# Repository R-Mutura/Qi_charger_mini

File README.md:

# The_Qi_wireless_charger_tx
This repo contains the design files for the Qi wireless charger.

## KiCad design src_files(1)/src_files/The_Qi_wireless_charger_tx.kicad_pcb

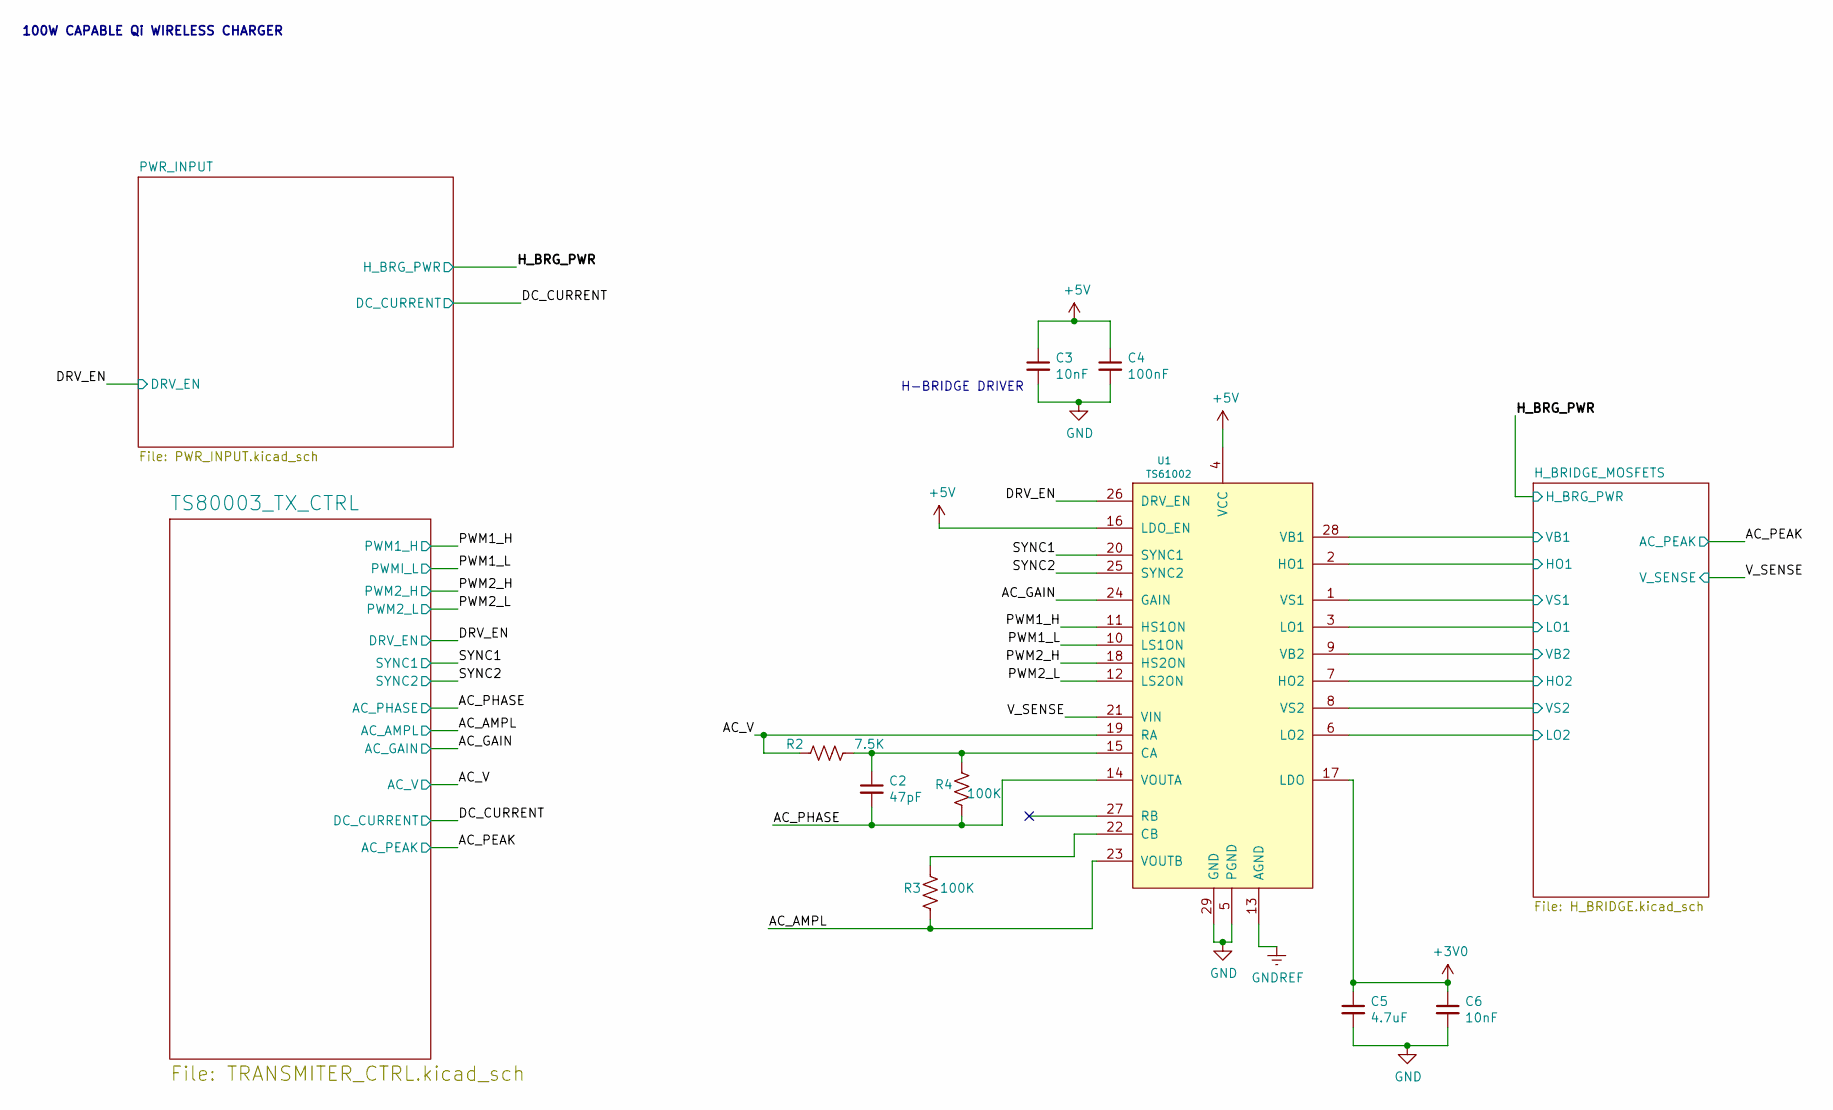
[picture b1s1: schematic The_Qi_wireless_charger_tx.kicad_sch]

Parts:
C2: 47pF; C_0402_1005Metric
C3, C6: 10nF; C_0402_1005Metric
C4: 100nF; C_0402_1005Metric
C5: 4.7uF; C_0402_1005Metric
R2: 7.5K; R_0402_1005Metric
R3, R4: 100K; R_0402_1005Metric
U1: TS61002; QFN50P500X500X100-29N

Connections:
+3V0: C5.1, C6.1, U1.17 (LDO)
+5V: C3.1, C4.1, U1.4 (VCC), U1.16 (LDO_EN); also elsewhere on the board
/AC_AMPL: R3.2, U1.23 (VOUTB); also elsewhere on the board
/AC_GAIN: U1.24 (GAIN); also elsewhere on the board
/AC_PHASE: C2.2, R4.2, U1.14 (VOUTA); also elsewhere on the board
/AC_V: R2.1, U1.19 (RA); also elsewhere on the board
/DRV_EN: U1.26 (DRV_EN); also elsewhere on the board
/H_BRIDGE_MOSFETS/HO1: U1.2 (HO1); also elsewhere on the board
/H_BRIDGE_MOSFETS/HO2: U1.7 (HO2); also elsewhere on the board
/H_BRIDGE_MOSFETS/LO1: U1.3 (LO1); also elsewhere on the board
/H_BRIDGE_MOSFETS/LO2: U1.6 (LO2); also elsewhere on the board
/H_BRIDGE_MOSFETS/VB1: U1.28 (VB1); also elsewhere on the board
/H_BRIDGE_MOSFETS/VB2: U1.9 (VB2); also elsewhere on the board
/H_BRIDGE_MOSFETS/VS1: U1.1 (VS1); also elsewhere on the board
/H_BRIDGE_MOSFETS/VS2: U1.8 (VS2); also elsewhere on the board
/PWM1_H: U1.11 (HS1ON); also elsewhere on the board
/PWM1_L: U1.10 (LS1ON); also elsewhere on the board
/PWM2_H: U1.18 (HS2ON); also elsewhere on the board
/PWM2_L: U1.12 (LS2ON); also elsewhere on the board
/SYNC1: U1.20 (SYNC1); also elsewhere on the board
/SYNC2: U1.25 (SYNC2); also elsewhere on the board
/V_SENSE: U1.21 (VIN); also elsewhere on the board
GND: C3.2, C4.2, C5.2, C6.2, U1.5 (PGND), U1.29 (GND); also elsewhere on the board
GNDREF: U1.13 (AGND); also elsewhere on the board
unnamed: C2.1, R2.2, R4.1, U1.15 (CA)
unnamed: R3.1, U1.22 (CB)

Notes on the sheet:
100W CAPABLE Qi WIRELESS CHARGER
H-BRIDGE DRIVER

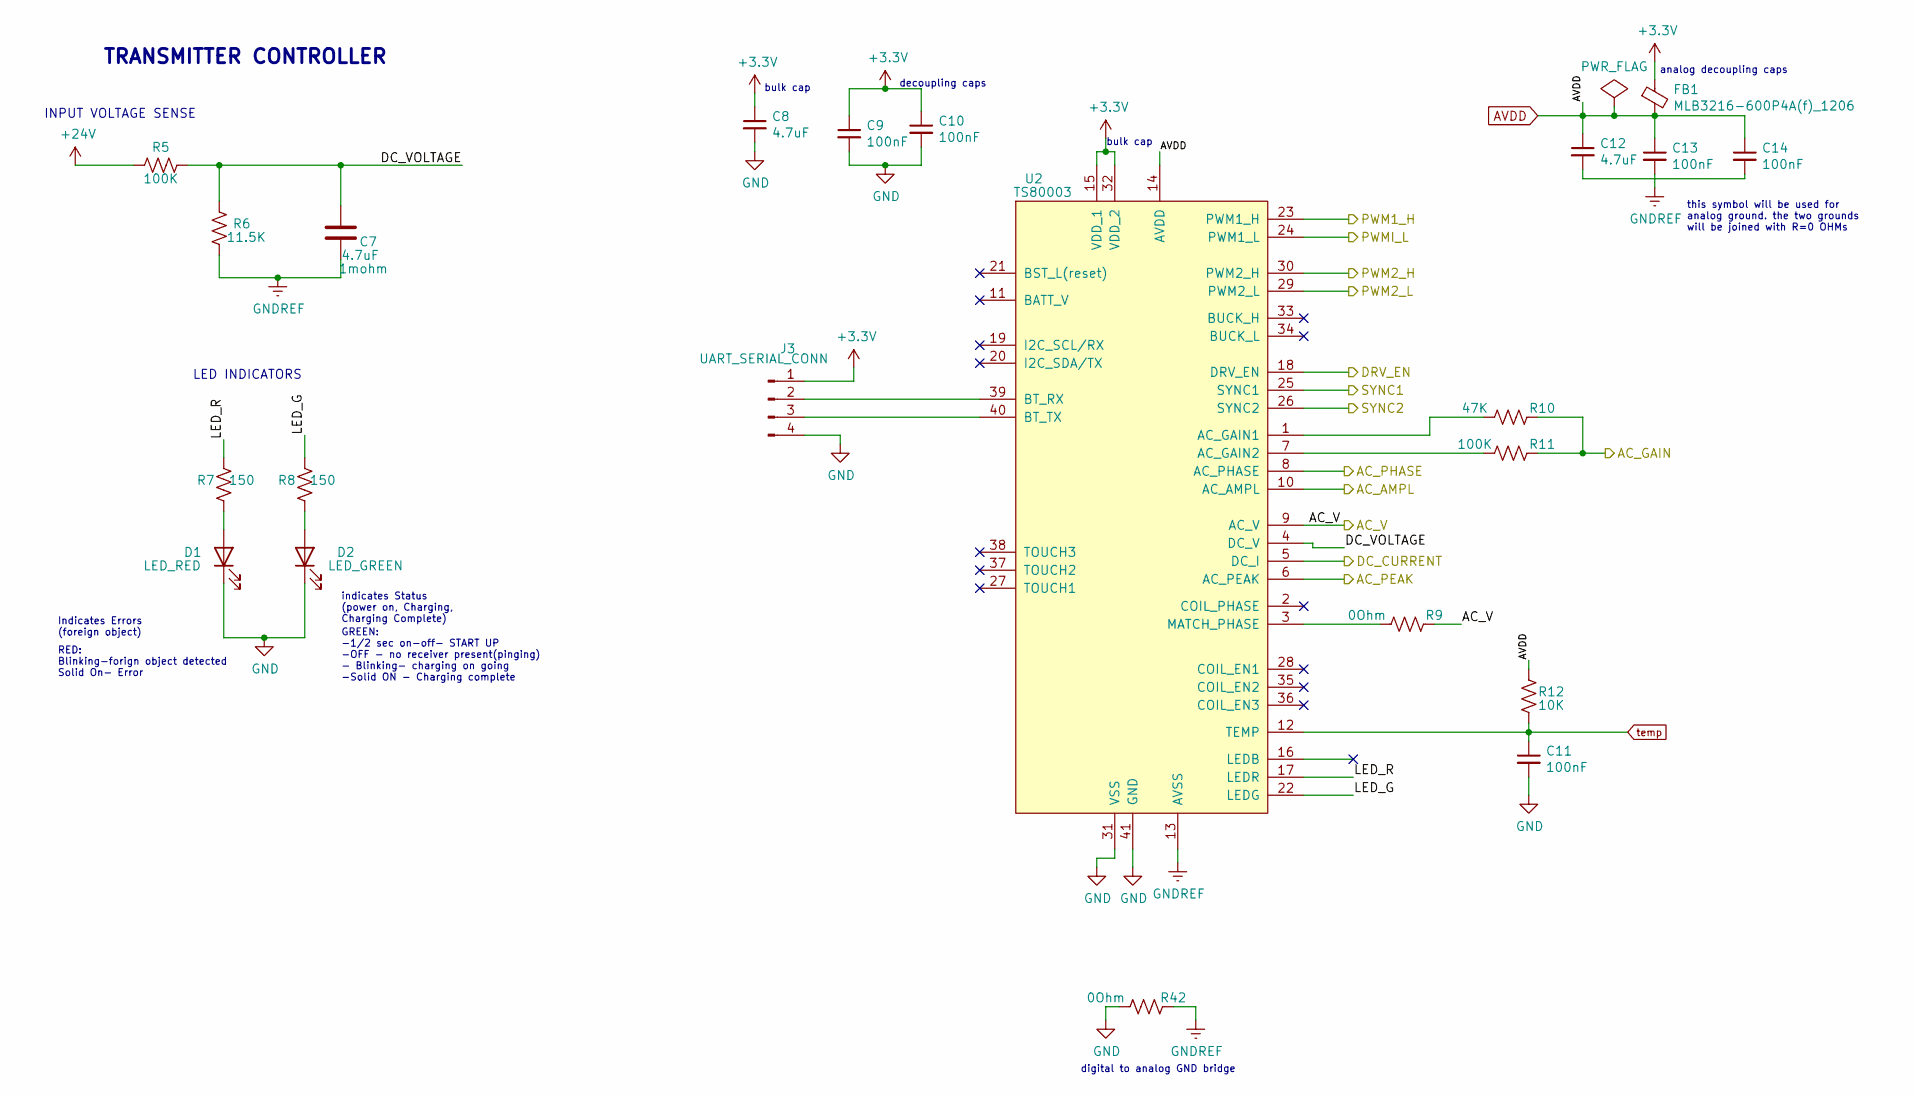
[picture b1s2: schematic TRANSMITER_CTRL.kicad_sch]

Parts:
C7, C8, C12: 4.7uF; C_0402_1005Metric
C9, C10, C11, C13, C14: 100nF; C_0402_1005Metric
D1: LED_RED; LED_0603_1608Metric
D2: LED_GREEN; LED_0603_1608Metric
FB1: MLB3216-600P4A(f)_1206; L_1206_3216Metric
J3: UART_SERIAL_CONN; PinHeader_1x04_P2.54mm_Vertical
R5, R11: 100K; R_0603_1608Metric
R6: 11.5K; R_0603_1608Metric
R7, R8: 150; R_0402_1005Metric
R9, R42: 0Ohm; R_0603_1608Metric
R10: 47K; R_0603_1608Metric
R12: 10K; R_0603_1608Metric
U2: TS80003; QFN40P500X500X90-41N-D

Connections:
+3V3: C8.1, C9.1, C10.1, FB1.1, J3.1, U2.15 (VDD_1), U2.32 (VDD_2); also elsewhere on the board
+24V: R5.2; also elsewhere on the board
/AC_AMPL: U2.10 (AC_AMPL); also elsewhere on the board
/AC_GAIN: R10.1, R11.1; also elsewhere on the board
/AC_PEAK: U2.6 (AC_PEAK); also elsewhere on the board
/AC_PHASE: U2.8 (AC_PHASE); also elsewhere on the board
/AC_V: R9.1, U2.9 (AC_V); also elsewhere on the board
/DC_CURRENT: U2.5 (DC_I); also elsewhere on the board
/DRV_EN: U2.18 (DRV_EN); also elsewhere on the board
/PWM1_H: U2.23 (PWM1_H); also elsewhere on the board
/PWM1_L: U2.24 (PWM1_L); also elsewhere on the board
/PWM2_H: U2.30 (PWM2_H); also elsewhere on the board
/PWM2_L: U2.29 (PWM2_L); also elsewhere on the board
/SYNC1: U2.25 (SYNC1); also elsewhere on the board
/SYNC2: U2.26 (SYNC2); also elsewhere on the board
/TS80003_TX_CTRL/DC_VOLTAGE: C7.1, R5.1, R6.2, U2.4 (DC_V)
/TS80003_TX_CTRL/LED_G: R8.1, U2.22 (LEDG)
/TS80003_TX_CTRL/LED_R: R7.1, U2.17 (LEDR)
AVDD: C12.1, C13.1, C14.1, FB1.2, R12.1, U2.14 (AVDD); also elsewhere on the board
GND: C8.2, C9.2, C10.2, C11.2, D1.1 (K), D2.1 (K), J3.4, R42.2, U2.31 (VSS), U2.41 (GND); also elsewhere on the board
GNDREF: C7.2, C13.2, R6.1, R42.1, U2.13 (AVSS); also elsewhere on the board
unnamed: C12.2, C14.2
unnamed: D1.2 (A), R7.2
unnamed: D2.2 (A), R8.2
unnamed: J3.2, U2.39 (BT_RX)
unnamed: J3.3, U2.40 (BT_TX)
unnamed: R9.2, U2.3 (MATCH_PHASE)
unnamed: R10.2, U2.1 (AC_GAIN1)
unnamed: R11.2, U2.7 (AC_GAIN2)
temp: C11.1, R12.2, U2.12 (TEMP); also elsewhere on the board

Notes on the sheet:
TRANSMITTER CONTROLLER
INPUT VOLTAGE SENSE
indicates Status (power on, Charging, Charging Complete)
digital to analog GND bridge
LED INDICATORS
analog decoupling caps
this symbol will be used for analog ground. the two grounds will be joined with R=0 OHMs
bulk cap
RED: Blinking-forign object detected Solid On- Error
decoupling caps
GREEN: -1/2 sec on-off- START UP -OFF - no receiver present(pinging) - Blinking- charging on going -Solid ON - Charging complete
Indicates Errors (foreign object)

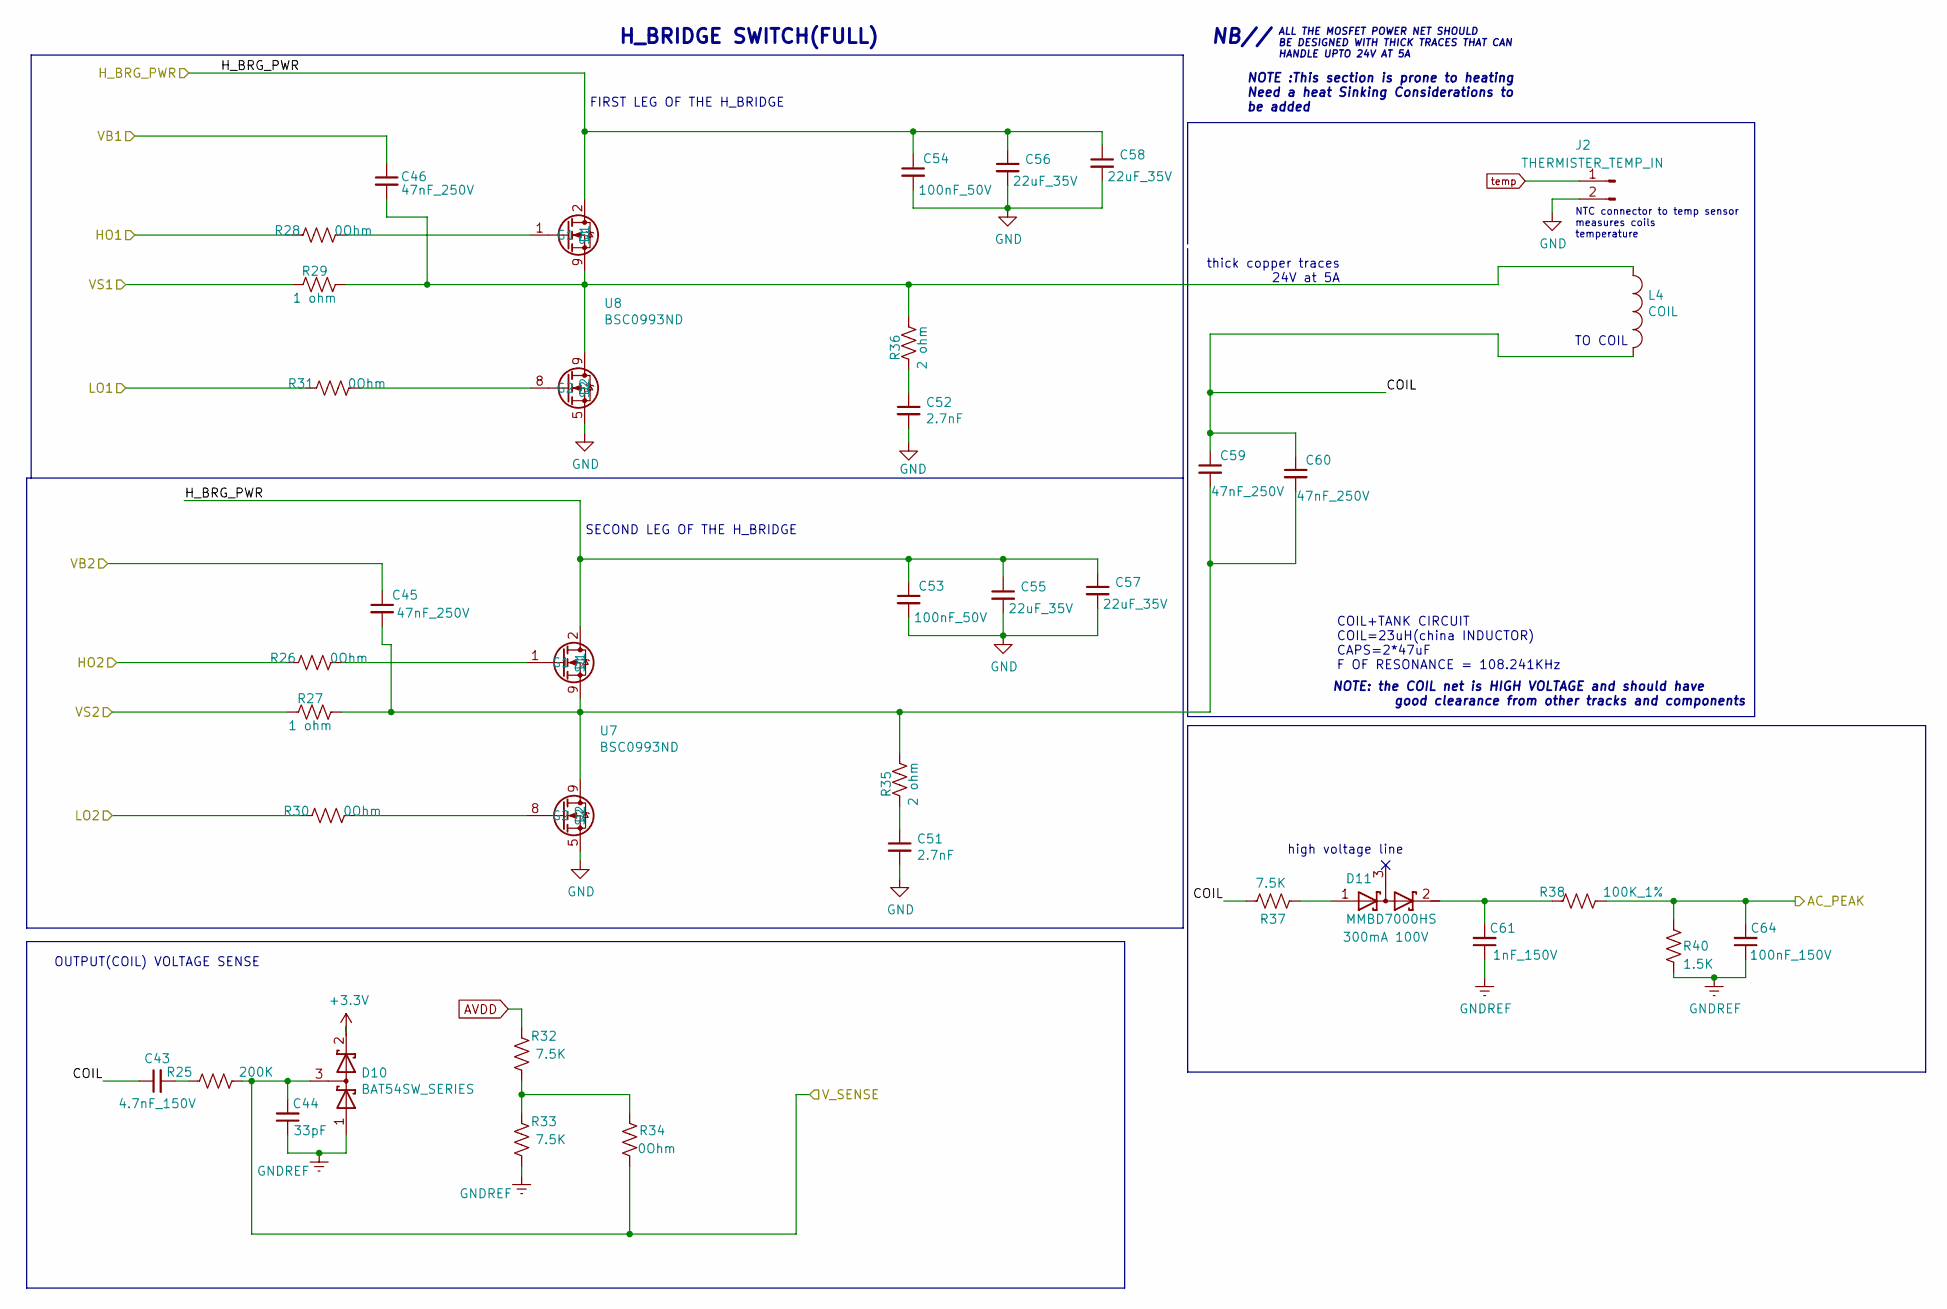
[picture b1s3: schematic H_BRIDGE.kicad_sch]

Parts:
C43: 4.7nF_150V; C_0805_2012Metric
C44: 33pF; C_0402_1005Metric
C45, C46, C59, C60: 47nF_250V; C_0805_2012Metric
C51, C52: 2.7nF; C_0402_1005Metric
C53, C54: 100nF_50V; C_0402_1005Metric
C55, C56, C57, C58: 22uF_35V; C_0805_2012Metric
C61: 1nF_150V; C_0603_1608Metric
C64: 100nF_150V; C_0805_2012Metric
D10: BAT54SW_SERIES; SOT-323_SC-70
D11: MMBD7000HS; SOT-23
J2: THERMISTER_TEMP_IN; JST_EH_B2B-EH-A_1x02_P2.50mm_Vertical
L4: COIL; coil_760308102144
R25: 200K; R_0603_1608Metric
R26, R28, R30, R31, R34: 0Ohm; R_0603_1608Metric
R27, R29: 1 ohm; R_0603_1608Metric
R32, R33: 7.5K; R_0402_1005Metric
R35, R36: 2 ohm; R_0603_1608Metric
R37: 7.5K; R_0805_2012Metric
R38: 100K_1%; R_0603_1608Metric
R40: 1.5K; R_1206_3216Metric
U7, U8: BSC0993ND

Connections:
+3V3: D10.2 (K); also elsewhere on the board
/AC_PEAK: C64.2, R38.2, R40.2; also elsewhere on the board
/H_BRG_PWR: C53.1, C54.1, C55.1, C56.1, C57.1, C58.1, U7.2 (D1), U7.3 (D1), U7.4 (D1), U8.2 (D1), U8.3 (D1), U8.4 (D1); also elsewhere on the board
/H_BRIDGE_MOSFETS/COIL: C43.1, C59.1, C60.1, L4.2, R37.1
/H_BRIDGE_MOSFETS/HO1: R28.1; also elsewhere on the board
/H_BRIDGE_MOSFETS/HO2: R26.1; also elsewhere on the board
/H_BRIDGE_MOSFETS/LO1: R31.1; also elsewhere on the board
/H_BRIDGE_MOSFETS/LO2: R30.1; also elsewhere on the board
/H_BRIDGE_MOSFETS/VB1: C46.1; also elsewhere on the board
/H_BRIDGE_MOSFETS/VB2: C45.1; also elsewhere on the board
/H_BRIDGE_MOSFETS/VS1: R29.2; also elsewhere on the board
/H_BRIDGE_MOSFETS/VS2: R27.2; also elsewhere on the board
/V_SENSE: C44.2, D10.3 (common), R25.2, R34.1; also elsewhere on the board
AVDD: R32.2; also elsewhere on the board
GND: C51.2, C52.2, C53.2, C54.2, C55.2, C56.2, C57.2, C58.2, J2.2, U7.5 (S2), U7.6 (S2), U7.7 (S2), U8.5 (S2), U8.6 (S2), U8.7 (S2); also elsewhere on the board
GNDREF: C44.1, C61.1, C64.1, D10.1 (A), R33.1, R40.1; also elsewhere on the board
unnamed: C43.2, R25.1
unnamed: C45.2, C59.2, C60.2, R27.1, R35.1, U7.9 (S1)
unnamed: C46.2, L4.1, R29.1, R36.1, U8.9 (S1)
unnamed: C51.1, R35.2
unnamed: C52.1, R36.2
unnamed: C61.2, D11.2 (K), R38.1
unnamed: D11.1 (A), R37.2
unnamed: R26.2, U7.1 (G1)
unnamed: R28.2, U8.1 (G1)
unnamed: R30.2, U7.8 (G2)
unnamed: R31.2, U8.8 (G2)
unnamed: R32.1, R33.2, R34.2
temp: J2.1; also elsewhere on the board

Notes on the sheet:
H_BRIDGE SWITCH(FULL)
COIL+TANK CIRCUIT COIL=23uH(china INDUCTOR) CAPS=2*47uF F OF RESONANCE = 108.241KHz
NOTE :This section is prone to heating Need a heat Sinking Considerations to be added
NOTE: the COIL net is HIGH VOLTAGE and should have good clearance from other tracks and components
FIRST LEG OF THE H_BRIDGE
NTC connector to temp sensor measures coils temperature
ALL THE MOSFET POWER NET SHOULD BE DESIGNED WITH THICK TRACES THAT CAN HANDLE UPTO 24V AT 5A
NB//
thick copper traces 24V at 5A
OUTPUT(COIL) VOLTAGE SENSE
high voltage line
TO COIL
SECOND LEG OF THE H_BRIDGE

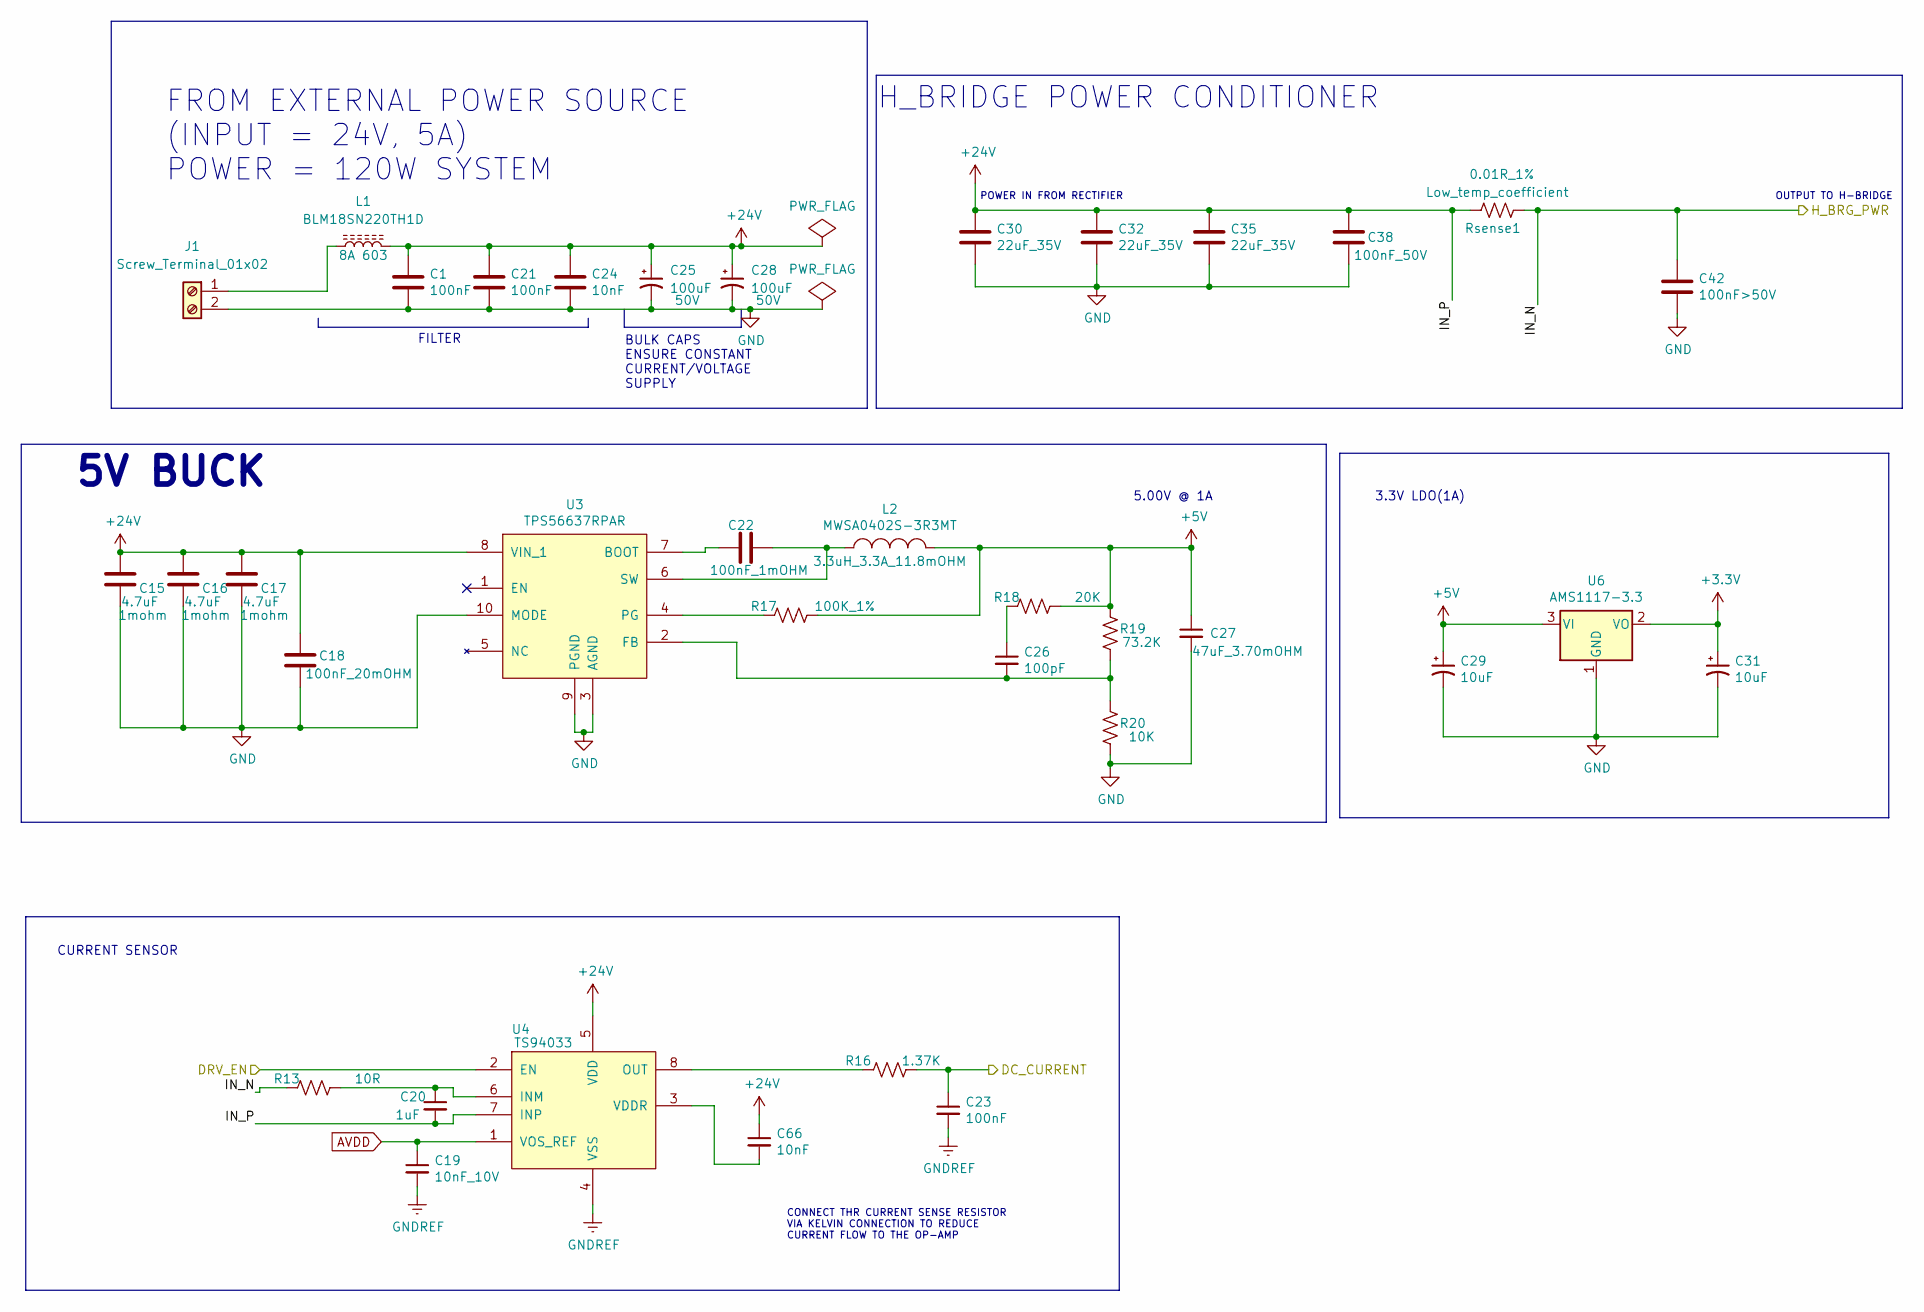
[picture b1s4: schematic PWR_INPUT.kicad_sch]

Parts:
C1, C21: 100nF; C_0603_1608Metric
C15, C16, C17: 4.7uF; C_0603_1608Metric
C18: 100nF_20mOHM; C_0402_1005Metric
C19: 10nF_10V; C_0402_1005Metric
C20: 1uF; C_0402_1005Metric
C22: 100nF_1mOHM; C_0402_1005Metric
C23: 100nF; C_0402_1005Metric
C24: 10nF; C_0603_1608Metric
C25, C28: 100uF; CP_Elec_6.3x7.7; MPN VZT101M1HTR-0607
C26: 100pF; C_0402_1005Metric
C27: 47uF_3.70mOHM; C_0603_1608Metric
C29, C31: 10uF; CP_EIA-2012-12_Kemet-R
C30, C32, C35: 22uF_35V; C_1206_3216Metric
C38: 100nF_50V; C_0402_1005Metric
C42: 100nF>50V; C_0402_1005Metric
C66: 10nF; C_0402_1005Metric
J1: Screw_Terminal_01x02; TerminalBlock_MetzConnect_Type101_RT01602HBWC_1x02_P5.08mm_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
L1: BLM18SN220TH1D; L_0603_1608Metric
L2: MWSA0402S-3R3MT; MWSA0402-xxx
R13: 10R; R_0402_1005Metric
R16: 1.37K; R_0402_1005Metric
R17: 100K_1%; R_0603_1608Metric
R18: 20K; R_0603_1608Metric
R19: 73.2K; R_0603_1608Metric
R20: 10K; R_0603_1608Metric
Rsense1: 0.01R_1%; R_0805_2012Metric
U3: TPS56637RPAR
U4: TS94033; SOT65P280X145-8N
U6: AMS1117-3.3; SOT-223-3_TabPin2

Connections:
+3V3: C31.1, U6.2 (VO); also elsewhere on the board
+5V: C27.1, C29.1, L2.2, R17.2, R18.2, R19.2, U6.3 (VI); also elsewhere on the board
+24V: C1.1, C15.1, C16.1, C17.1, C18.1, C20.2, C21.1, C24.1, C25.1, C28.1, C30.1, C32.1, C35.1, C38.1, C66.1, L1.2, Rsense1.1, U3.8 (VIN_1), U3.11 (VIN_2), U3.12 (VIN_3), U3.13 (VIN_4), U4.5 (VDD), U4.7 (INP); also elsewhere on the board
/DC_CURRENT: C23.1, R16.1; also elsewhere on the board
/DRV_EN: U4.2 (EN); also elsewhere on the board
/H_BRG_PWR: C42.1, R13.1, Rsense1.2; also elsewhere on the board
AVDD: C19.1, U4.1 (VOS_REF); also elsewhere on the board
GND: C1.2, C15.2, C16.2, C17.2, C18.2, C21.2, C24.2, C25.2, C27.2, C28.2, C29.2, C30.2, C31.2, C32.2, C35.2, C38.2, C42.2, J1.2, R20.1, U3.3 (AGND), U3.9 (PGND), U3.10 (MODE), U6.1 (GND); also elsewhere on the board
GNDREF: C19.2, C23.2, U4.4 (VSS); also elsewhere on the board
unnamed: C20.1, R13.2, U4.6 (INM)
unnamed: C22.1, U3.7 (BOOT)
unnamed: C22.2, L2.1, U3.6 (SW)
unnamed: C26.1, R18.1
unnamed: C26.2, R19.1, R20.2, U3.2 (FB)
unnamed: C66.2, U4.3 (VDDR)
unnamed: J1.1, L1.1
unnamed: R16.2, U4.8 (OUT)
unnamed: R17.1, U3.4 (PG)

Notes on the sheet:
OUTPUT TO H-BRIDGE
5.00V @ 1A
BULK CAPS ENSURE CONSTANT CURRENT/VOLTAGE SUPPLY
POWER IN FROM RECTIFIER
FROM EXTERNAL POWER SOURCE (INPUT = 24V, 5A) POWER = 120W SYSTEM
FILTER
H_BRIDGE POWER CONDITIONER
CONNECT THR CURRENT SENSE RESISTOR VIA KELVIN CONNECTION TO REDUCE CURRENT FLOW TO THE OP-AMP
3.3V LDO(1A)
5V BUCK
CURRENT SENSOR

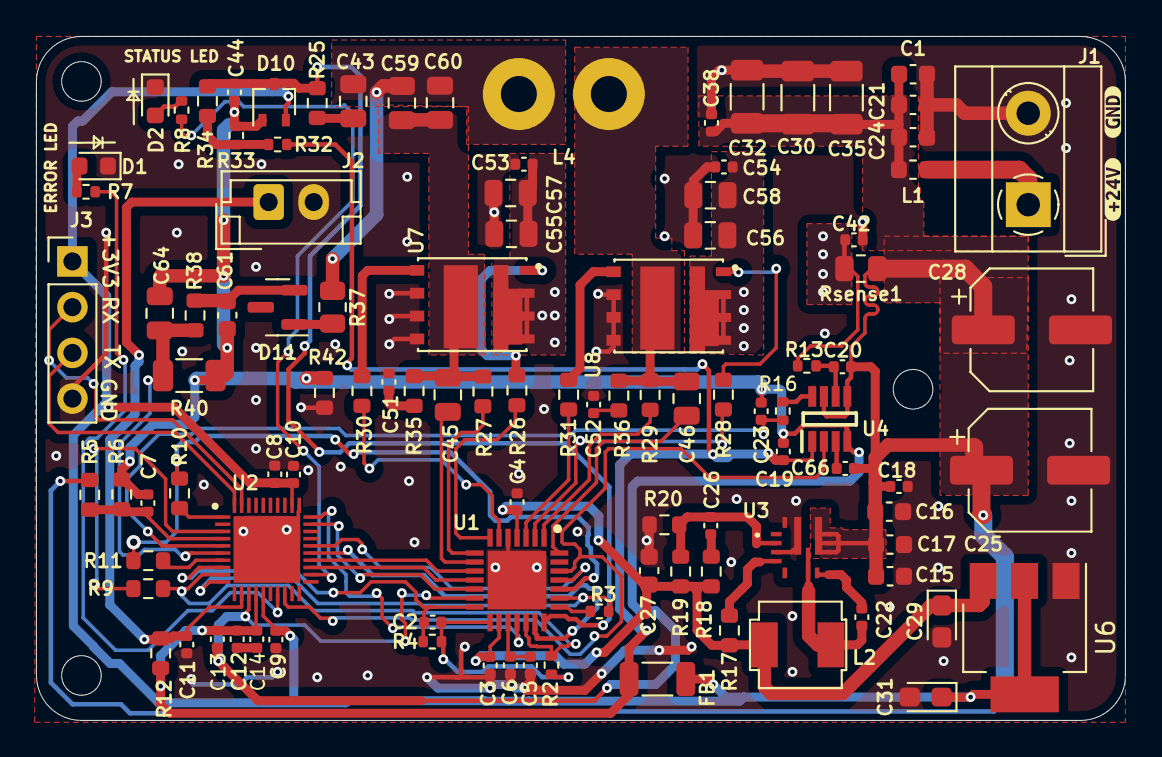
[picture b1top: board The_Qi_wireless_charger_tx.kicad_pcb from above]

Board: 2 copper layers, 60.5 x 38.0 mm, 106 parts (0 on the bottom side), 66 nets.

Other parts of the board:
kibuzzard-628BC247: G***; kibuzzard-628BC247
kibuzzard-628BC257: G***; kibuzzard-628BC257

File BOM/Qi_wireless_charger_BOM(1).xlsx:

Reference | Value | Footprint | MPN | Vendor | QTY
C1, C21 | 100nF | Capacitor_SMD:C_0603_1608Metric | 0603B104K500NT | LCSC | 2
C2 | 47pF | Capacitor_SMD:C_0402_1005Metric | CC0402JRNPO9BN470 | LCSC | 1
C4, C9-C11, C13, C14, C23 | 100nF | Capacitor_SMD:C_0402_1005Metric | CC0402JRNPO9BN470 | LCSC | 7
C5, C7, C8, C12 | 4.7uF | Capacitor_SMD:C_0402_1005Metric | CL05A475KP5NRNC | LCSC | 4
C3, C6, C66 | 10nF | Capacitor_SMD:C_0402_1005Metric | CL05B103KB5NNNC | LCSC | 3
C15-C17 | 4.7uF | Capacitor_SMD:C_0603_1608Metric | CL10A475KL8NRNC | LCSC | 3
C18 | 100nF_20mOHM | Capacitor_SMD:C_0402_1005Metric | CC0402JRNPO9BN470 | DigiKey | 1
C19 | 10nF_10V | Capacitor_SMD:C_0402_1005Metric | CL05B103KB5NNNC | LCSC | 1
C20 | 1uF | Capacitor_SMD:C_0402_1005Metric | CL05A105KP5NNNC | LCSC | 1
C22 | 100nF_1mOHM | Capacitor_SMD:C_0402_1005Metric | CC0402KRX7R7BB104 | LCSC | 1
C24 | 10nF | Capacitor_SMD:C_0603_1608Metric | 0603B104K500NT | LCSC | 1
C26 | 100pF | Capacitor_SMD:C_0402_1005Metric | CC0402KRX7R7BB104 | LCSC | 1
C27 | 47uF_3.70mOHM | Capacitor_SMD:C_0603_1608Metric | GRM188R60J476ME15D | LCSC | 1
C25, C28 | 100uF | Capacitor_SMD:CP_Elec_6.3x7.7 | VZT101M1HTR-0607 | LCSC | 2
C29, C31 | 10uF | Capacitor_Tantalum_SMD:CP_EIA-2012-12_Kemet-R | TAJR106K006RNJ | LCSC | 2
C30, C32, C35 | 22uF_35V | Capacitor_SMD:C_1206_3216Metric | C3216X5R1V226MTJ00E | LCSC | 3
C38, C53, C54 | 100nF_50V | Capacitor_SMD:C_0402_1005Metric | 0402F104M500NT | LCSC | 3
C42 | 100nF>50V | Capacitor_SMD:C_0402_1005Metric | 0402F104M500NT | LCSC | 1
C43 | 4.7nF_150V | Capacitor_SMD:C_0805_2012Metric | C0805C472K2RECAUTO | DigiKey | 1
C44 | 33pF | Capacitor_SMD:C_0402_1005Metric | CC0805JRNPOABN330 | DigiKey | 1
C51, C52 | 2.7nF | Capacitor_SMD:C_0402_1005Metric | 0402B272K500NT | LCSC | 2
C55-C58 | 22uF_35V | Capacitor_SMD:C_0805_2012Metric | C3216X5R1V226MTJ00E | LCSC | 4
C45, C46, C59, C60 | 47nF_250V | Capacitor_SMD:C_0805_2012Metric | C2012X7T2E473KT000N | LCSC | 4
C61 | 1nF_150V | Capacitor_SMD:C_0603_1608Metric | 0603B102K201CT | LCSC | 1
C64 | 100nF_150V | Capacitor_SMD:C_0805_2012Metric | FM21X104K201ECG | LCSC | 1
D1 | LED_RED | LED_SMD:LED_0603_1608Metric | SZYY0603R | LCSC | 1
D2 | LED_GREEN | LED_SMD:LED_0603_1608Metric | XZVGMDK53W-9 | LCSC | 1
D10 | BAT54SW_SERIES | Package_TO_SOT_SMD:SOT-323_SC-70 | BAT60B | LCSC | 1
D11 | MMBD7000HS | Package_TO_SOT_SMD:SOT-23 | MMBD7000HS | DigiKey | 1
FB1 | MLB3216-600P4A(f)_1206 | Inductor_SMD:L_1206_3216Metric | MLB3216-600P4A(f) | LCSC | 1
J1 | Screw_Terminal_01x02 | TerminalBlock_MetzConnect:TerminalBlock_MetzConnect_Type101_RT01602HBWC_1x02_P5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 | DB128L-5.08-2P-GN-P | LCSC | 1
J2 | THERMISTER_TEMP_IN | Connector_JST:JST_EH_B2B-EH-A_1x02_P2.50mm_Vertical | B2B-XH-A(LF)(SN) |  | 1
J3 | UART_SERIAL_CONN | Connector_PinHeader_2.54mm:PinHeader_1x04_P2.54mm_Vertical | B-2100S04P-A110 | LCSC | 1
L1 | BLM18SN220TH1D | Inductor_SMD:L_0603_1608Metric | BLM18SN220TH1D | LCSC | 1
L2 | MWSA0402S-3R3MT | greencharge-footprints:MWSA0402-xxx | MWSA0402S-3R3MT | DigiKey | 1
R2, R32, R33 | 7.5K | Resistor_SMD:R_0402_1005Metric | RC-02W1003FT | LCSC | 3
R3, R4 | 100K | Resistor_SMD:R_0402_1005Metric | RS-06K1003FT | LCSC | 2
R5, R11 | 100K | Resistor_SMD:R_0603_1608Metric | RC0603FR-07100KL | LCSC | 2
R6 | 11.5K | Resistor_SMD:R_0603_1608Metric | 0603WAF1152T5E | LCSC | 1
R7, R8 | 150 | Resistor_SMD:R_0402_1005Metric | 0402WGF1500TCE | LCSC | 2
R10 | 47K | Resistor_SMD:R_0603_1608Metric | 0603WAF4702T5E | LCSC | 1
R13 | 10R | Resistor_SMD:R_0402_1005Metric | 0402WGF1000TCE | LCSC | 1
R16 | 1.37K | Resistor_SMD:R_0402_1005Metric | 0402WGF1371TCE | LCSC | 1
R17, R38 | 100K_1% | Resistor_SMD:R_0603_1608Metric | RC0603FR-07100KL | LCSC | 2
R18 | 20K | Resistor_SMD:R_0603_1608Metric | 0603WAF2002T5E | LCSC | 1
R19 | 73.2K | Resistor_SMD:R_0603_1608Metric | ERJ3EKF7322V | LCSC | 1
R12, R20 | 10K | Resistor_SMD:R_0603_1608Metric | RC0603JR-0710KL | LCSC | 2
R25 | 200K | Resistor_SMD:R_0603_1608Metric | RC0603FR-07200KL | LCSC | 1
R27, R29 | 1 ohm | Resistor_SMD:R_0603_1608Metric | 0603WAF100KT5E | LCSC | 2
R35, R36 | 2 ohm | Resistor_SMD:R_0603_1608Metric | 0603WAF200KT5E | LCSC | 2
R37 | 7.5K | Resistor_SMD:R_0805_2012Metric | 0805W8F7501T5E | LCSC | 1
R40 | 1.5K | Resistor_SMD:R_1206_3216Metric | 1206W4J0102T5E | LCSC | 1
R9, R26, R28, R30, R31, R34, R42 | 0Ohm | Resistor_SMD:R_0603_1608Metric | 0603WAF0000T5E | LCSC | 7
Rsense1 | 0.01R_1% | Resistor_SMD:R_0805_2012Metric | RTT03R010JTP | LCSC | 1
U1 | TS61002 | greencharge-footprints:QFN50P500X500X100-29N | TS61002-QFNR | Mouser | 1
U2 | TS80003 | greencharge-footprints:QFN40P500X500X90-41N-D | TS80003-QFNR | Mouser | 1
U3 | TPS56637RPAR | greencharge-footprints:TPS56637RPAR | TPS56637RPAR | Digipart | 1
U4 | TS94033 | greencharge-footprints:SOT65P280X145-8N | TS94033 | Digipart | 1
U6 | AMS1117-3.3 | Package_TO_SOT_SMD:SOT-223-3_TabPin2 | AMS1117-3.3 | LCSC | 1
U7, U8 | BSC0993ND | greencharge-footprints:BSC0993ND | BSC0993NDATMA1 | Mouser | 2

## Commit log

2022-05-29 complete Qi charger project
